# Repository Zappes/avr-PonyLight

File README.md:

Das PonyLight
============

Was isses?
-------------

Das PonyLight ist ein simpler Controller für RGB-LED-Streifen, der es erlaubt, die Streifenfarbe über USB zu steuern. Das sieht etwa so aus:

Zum PonyLight gibt es auch ein paar Videos, und zwar hier:

 - [Erstes Video](http://youtu.be/obpAEXGJzy8)
 - [Zweites Video](http://youtu.be/9RLEF0E1XvM)

Der Firmware-Code ist gnadenlos von [Pauls Rogalinskis TinyRGB](https://github.com/pulsar256/tinyrgb) geklaut. Wahrscheinlich habe ich neue Bugs reingeballert und alte nicht gefixt - im Zweifelsfall forkt Ihr besser seinen Code als meinen.

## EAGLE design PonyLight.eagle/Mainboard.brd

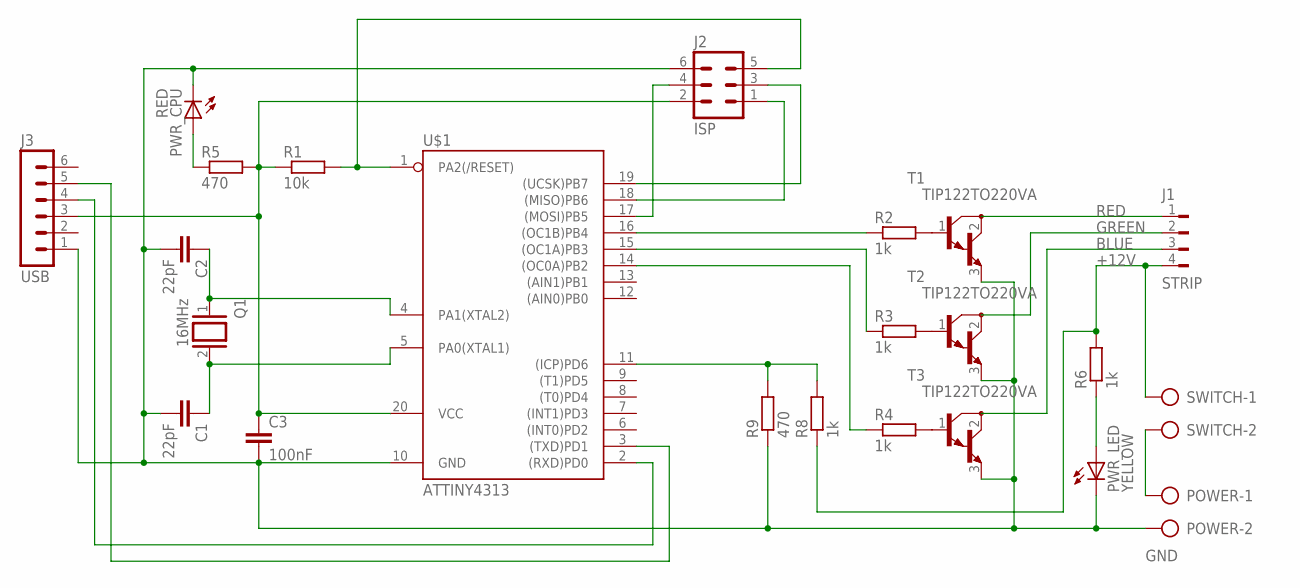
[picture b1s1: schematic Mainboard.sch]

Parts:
C1, C2: 22pF; C025-024X044
C3: 100nF; C025-024X044
J1: STRIP; FLOP-4V
J2: ISP; ML6
J3: USB; MA06-1
POWER: AK500/2
PWR_CPU: RED; LED2X5
PWR_LED: YELLOW; LED2X5
Q1: 16MHz; QS
R1: 10k; 0204/7
R2, R3, R4, R6, R8: 1k; 0204/7
R5, R9: 470; 0204/7
SWITCH: AK500/2
T1, T2, T3: TIP122TO220VA; TO220AV
U$1: ATTINY4313; DIL20

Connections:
+5V: C3.1, J2.2, J3.3, R1.1, R5.2, U$1.20 (VCC)
+12V: J1.4, R6.2, R8.1, SWITCH.1
BLUE: J1.3, T3.2 (C)
BLUE_PWM: R4.1, U$1.14 ((OC0A)PB2)
GND: C1.2, C2.2, C3.2, J2.6, J3.1, POWER.2, PWR_CPU.K (C), PWR_LED.K (C), R9.1, T1.3 (E), T2.3 (E), T3.3 (E), U$1.10 (GND)
GREEN: J1.2, T2.2 (C)
GREEN_PWM: R3.1, U$1.15 ((OC1A)PB3)
MISO: J2.1, U$1.18 ((MISO)PB6)
unnamed: J3.4, U$1.2 ((RXD)PD0)
unnamed: J3.5, U$1.3 ((TXD)PD1)
unnamed: PWR_CPU.A, R5.1
unnamed: R2.2, T1.1 (B)
unnamed: R3.2, T2.1 (B)
unnamed: R4.2, T3.1 (B)
unnamed: POWER.1, SWITCH.2
unnamed: J2.4, U$1.17 ((MOSI)PB5)
unnamed: PWR_LED.A, R6.1
RED: J1.1, T1.2 (C)
RED_PWM: R2.1, U$1.16 ((OC1B)PB4)
RESET: J2.5, R1.2, U$1.1 (PA2(/RESET))
SCK: J2.3, U$1.19 ((UCSK)PB7)
SENSE12V: R8.2, R9.2, U$1.11 ((ICP)PD6)
XTAL1: C1.1, Q1.2, U$1.5 (PA0(XTAL1))
XTAL2: C2.1, Q1.1, U$1.4 (PA1(XTAL2))

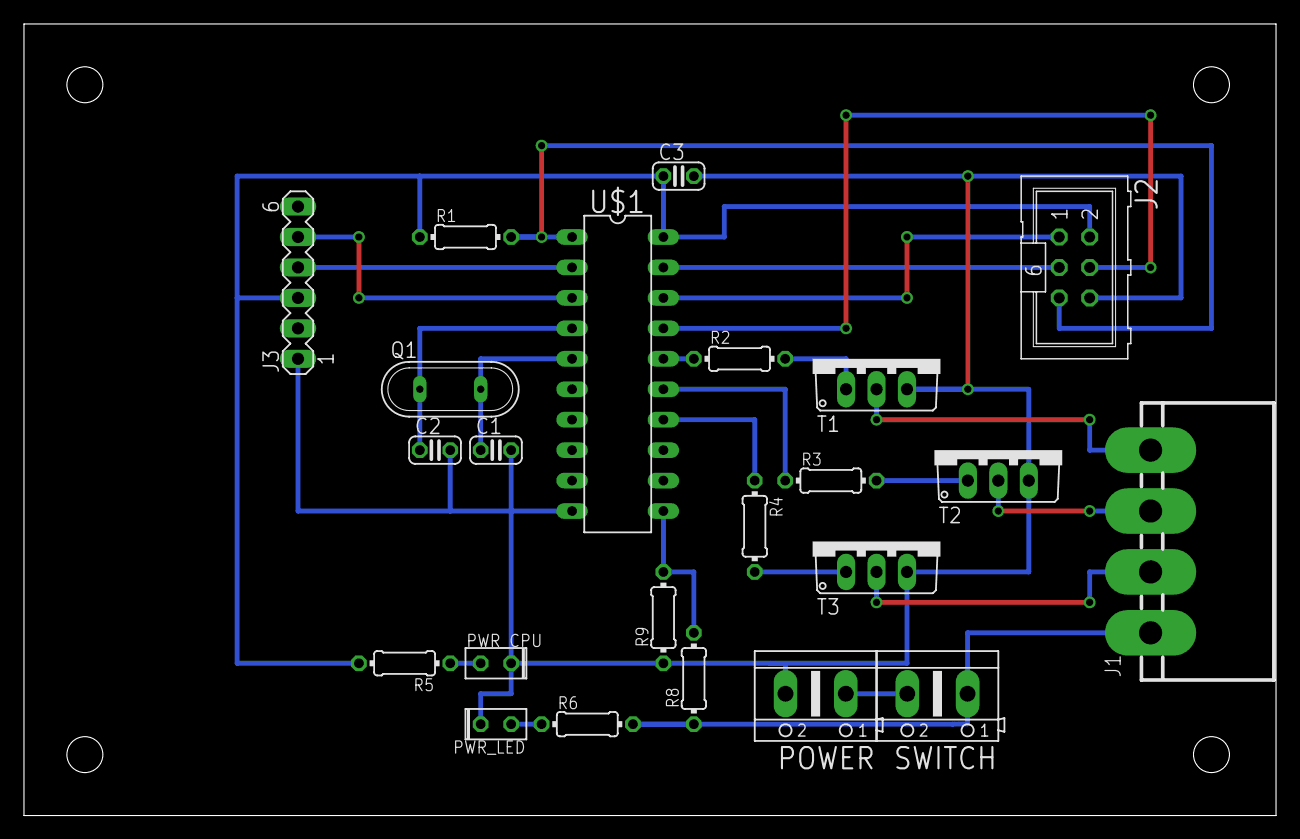
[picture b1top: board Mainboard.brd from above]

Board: 2 copper layers, 104.4 x 66.0 mm, 23 parts (0 on the bottom side), 24 nets.

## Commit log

2014-11-14 Added Schematic as a picture
2014-11-17 README added
2014-11-23 add ponytool
2014-12-16 render time as colour
2014-12-16 add minutely and hourly mode
2014-12-16 fix validation
